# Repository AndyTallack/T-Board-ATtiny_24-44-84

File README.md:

T-Board-Atiny 24/44/84
======================

T-Board for use on Breadboard - Attiny 24/44/84

This is a series of boards to speed up development of your own standalone ATMega/ATTiny projects.  The T-Board houses the microprocessor, power-supply and FTDI interface, with a breadboard-compatible footprint.  This allows you to get up and running fast with the core ATMega/ATTiny "heart" of your project.

This board is based on the great Arduino concept, and is compatible with the Arduino IDE.  It differs in that it:
- allows you to switch between 3.3V and 5V
- allows you to select crystals for low-power applications
- fits snugly into a breadboard, keeping your project together

There are 2 sets of schematic:
- T-Board-44-84 Etch:	1-layer, for hand-etching.  No ICSP header
- T-Board-44-84 PCB:	2-layer, for production-house.  With ICSP header

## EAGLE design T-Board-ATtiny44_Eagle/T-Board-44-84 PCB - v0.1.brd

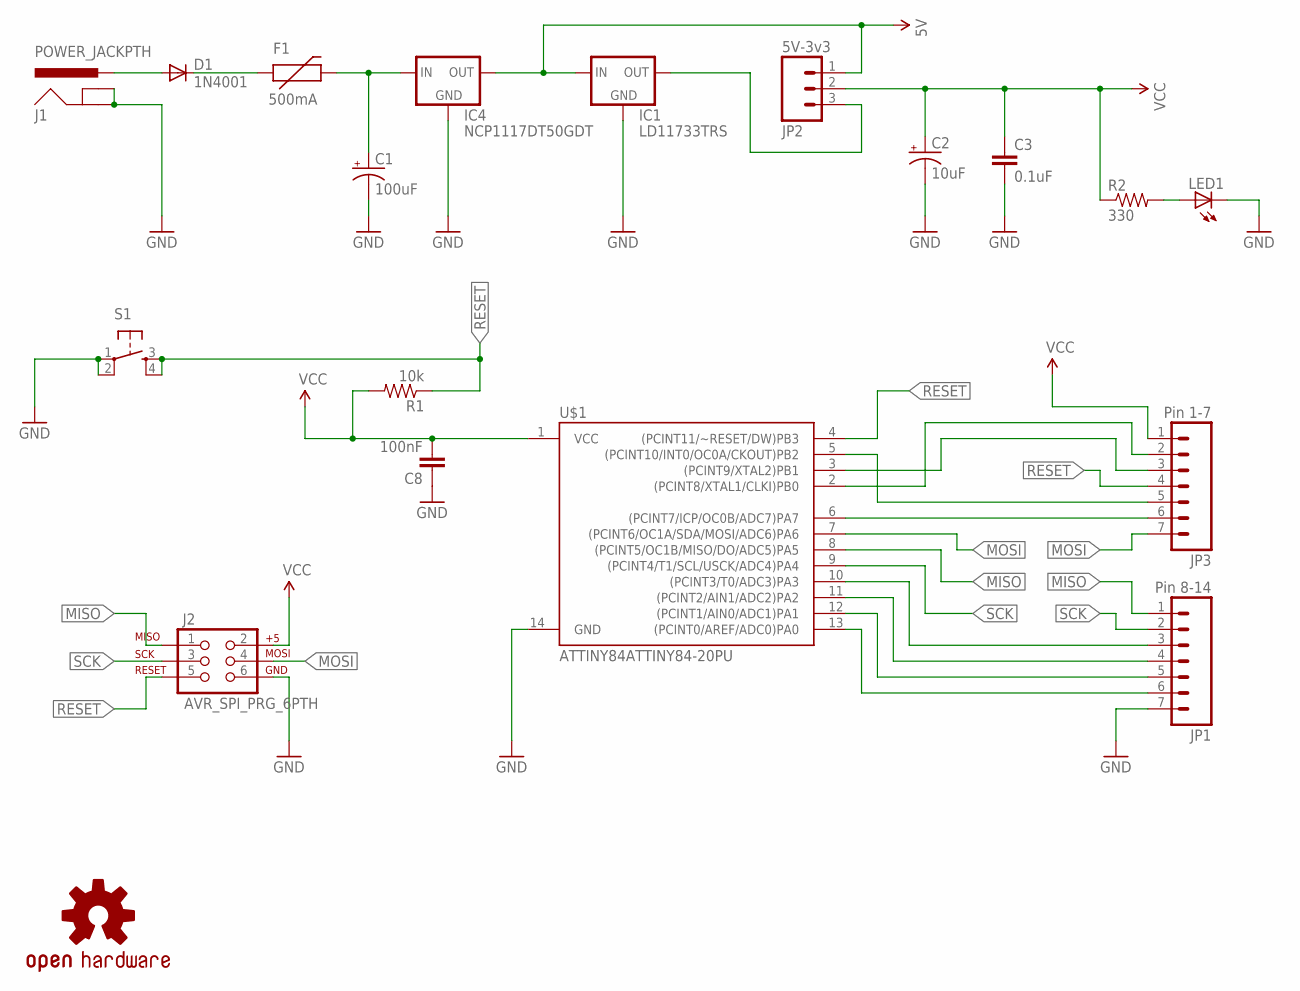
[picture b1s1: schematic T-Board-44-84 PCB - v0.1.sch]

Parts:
C1: 100uF; CPOL-RADIAL-100UF-25V
C2: 10uF; CPOL-RADIAL-10UF-25V
C3: 0.1uF; 1206
C8: 100nF; 1206
D1: 1N4001; DIODE-1N4001
F1: 500mA; PTC
IC1: LD11733TRS; SOT223
IC4: NCP1117DT50GDT; DPACK
J1: POWER_JACKPTH; POWER_JACK_PTH
J2: AVR_SPI_PRG_6PTH; 2X3
JP1: Pin 8-14; 1X07
JP2: 5V-3v3; 1X03
JP3: Pin 1-7; 1X07
LED1: LED1206; LED-1206
LOGO1: OSHW-LOGOS; OSHW-LOGO-S
R1: 10k; 1206
R2: 330; 1206
S1: TAC_SWITCHPTH; TACTILE-PTH
U$1: ATTINY84ATTINY84-20PU; DIL14

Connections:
5V: IC1.3 (IN), IC4.4 (OUT), JP2.1
GND: C1.2 (-), C2.2 (-), C3.2, C8.1, IC1.1 (GND), IC4.1 (GND), J1.GND, J1.GNDBREAK, J2.6, JP1.7, LED1.C, S1.1, S1.2, U$1.14 (GND)
MISO: J2.1, JP1.1, U$1.8 ((PCINT5/OC1B/MISO/DO/ADC5)PA5)
MOSI: J2.4, JP3.7, U$1.7 ((PCINT6/OC1A/SDA/MOSI/ADC6)PA6)
unnamed: D1.A, J1.PWR
unnamed: D1.C, F1.P$1 (1)
unnamed: C1.1 (+), F1.P$2 (2), IC4.3 (IN)
unnamed: JP3.2, U$1.2 ((PCINT8/XTAL1/CLKI)PB0)
unnamed: JP3.3, U$1.3 ((PCINT9/XTAL2)PB1)
unnamed: JP3.5, U$1.5 ((PCINT10/INT0/OC0A/CKOUT)PB2)
unnamed: JP3.6, U$1.6 ((PCINT7/ICP/OC0B/ADC7)PA7)
unnamed: LED1.A, R2.2
unnamed: IC1.4 (OUT), JP2.3
unnamed: JP1.3, U$1.10 ((PCINT3/T0/ADC3)PA3)
unnamed: JP1.4, U$1.11 ((PCINT2/AIN1/ADC2)PA2)
unnamed: JP1.5, U$1.12 ((PCINT1/AIN0/ADC1)PA1)
unnamed: JP1.6, U$1.13 ((PCINT0/AREF/ADC0)PA0)
RESET: J2.5, JP3.4, R1.1, S1.3, S1.4, U$1.4 ((PCINT11/~RESET/DW)PB3)
SCK: J2.3, JP1.2, U$1.9 ((PCINT4/T1/SCL/USCK/ADC4)PA4)
VCC: C2.1 (+), C3.1, C8.2, J2.2, JP2.2, JP3.1, R1.2, R2.1, U$1.1 (VCC)

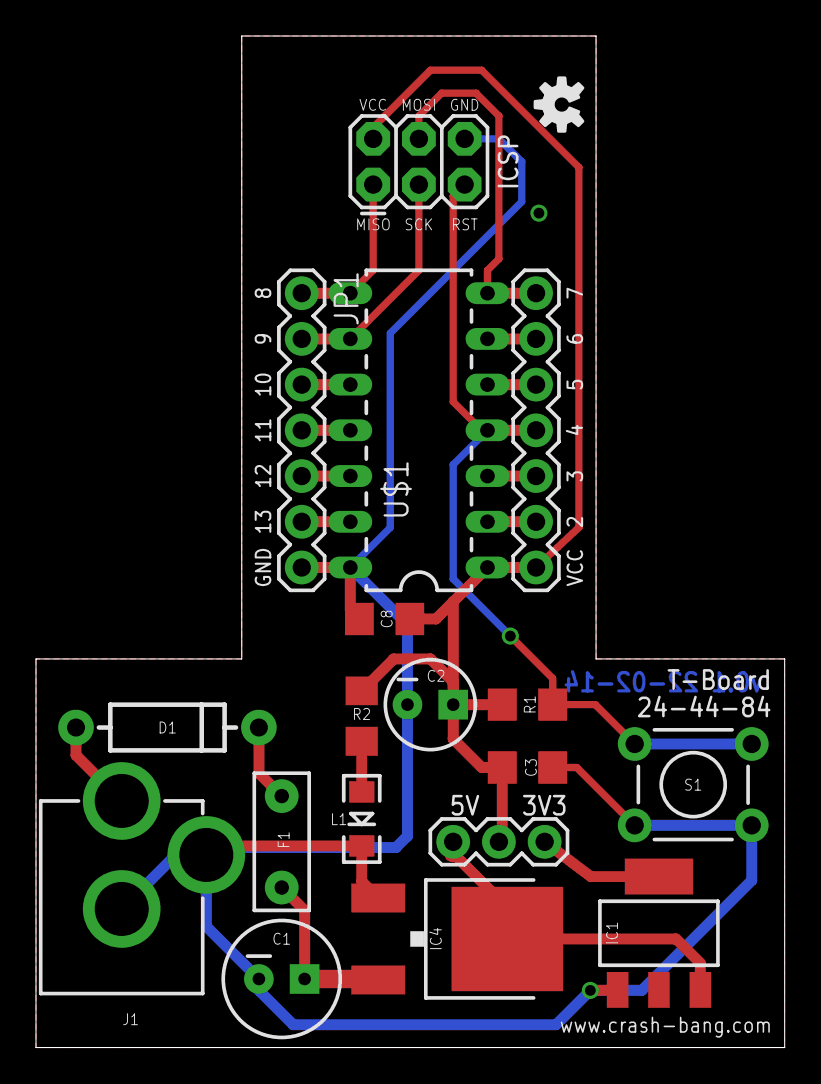
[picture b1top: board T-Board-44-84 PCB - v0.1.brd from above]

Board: 2 copper layers, 41.6 x 56.2 mm, 19 parts (0 on the bottom side), 20 nets.

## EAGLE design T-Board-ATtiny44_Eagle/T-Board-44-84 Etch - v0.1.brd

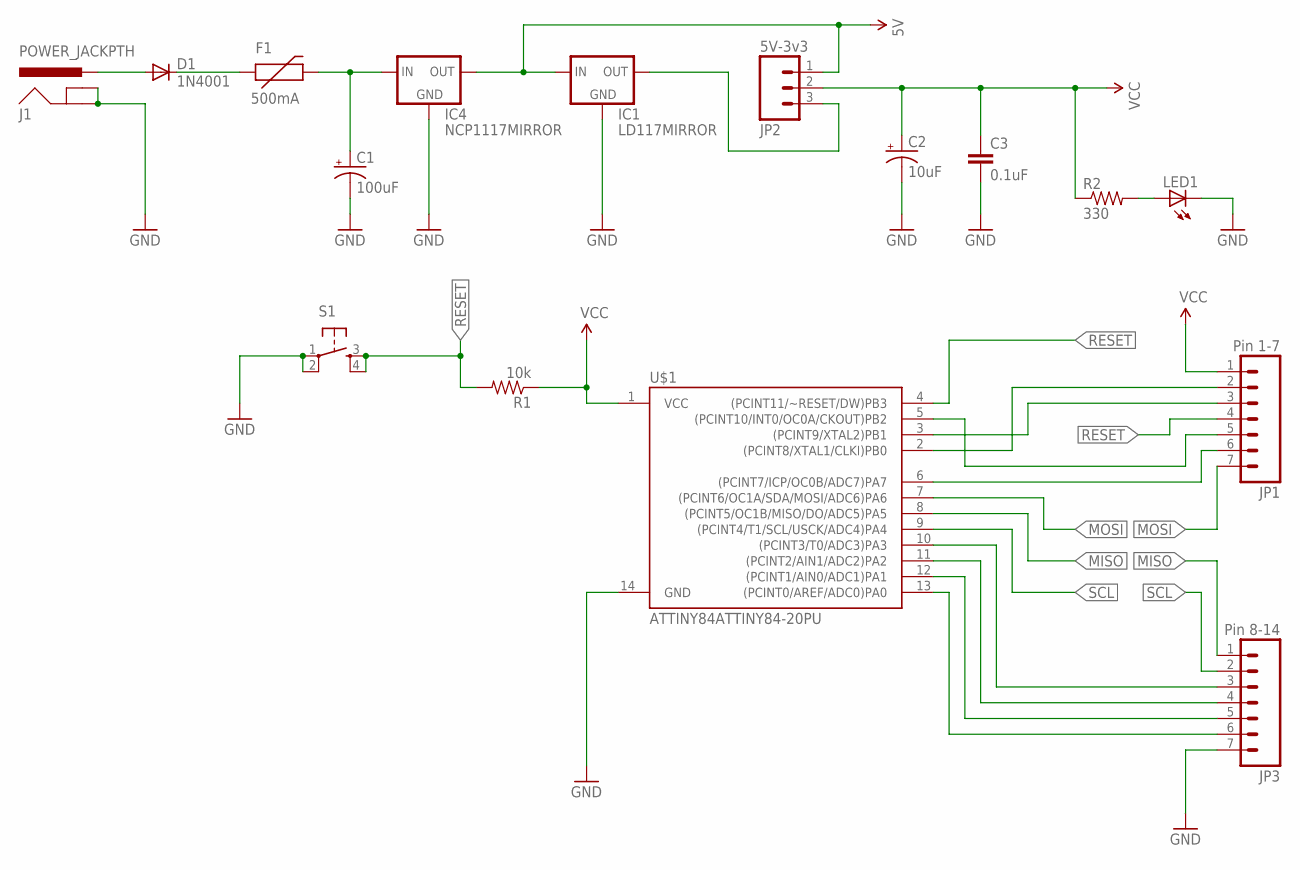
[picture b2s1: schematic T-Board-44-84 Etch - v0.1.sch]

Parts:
C1: 100uF; CPOL-RADIAL-100UF-25V
C2: 10uF; CPOL-RADIAL-10UF-25V
C3: 0.1uF; 1206
D1: 1N4001; DIODE-1N4001
F1: 500mA; PTC
IC1: LD117MIRROR; SOT223
IC4: NCP1117MIRROR; DPACK
J1: POWER_JACKPTH; POWER_JACK_PTH
JP1: Pin 1-7; 1X07
JP2: 5V-3v3; 1X03
JP3: Pin 8-14; 1X07
LED1: LED1206; LED-1206
R1: 10k; 1206
R2: 330; 1206
S1: TAC_SWITCHPTH; TACTILE-PTH
U$1: ATTINY84ATTINY84-20PU; DIL14

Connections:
5V: IC1.1 (IN), IC4.4 (OUT), JP2.1
GND: C1.2 (-), C2.2 (-), C3.2, IC1.3 (GND), IC4.3 (GND), J1.GND, J1.GNDBREAK, JP3.7, LED1.C, S1.1, S1.2, U$1.14 (GND)
MISO: JP3.1, U$1.8 ((PCINT5/OC1B/MISO/DO/ADC5)PA5)
MOSI: JP1.7, U$1.7 ((PCINT6/OC1A/SDA/MOSI/ADC6)PA6)
unnamed: D1.A, J1.PWR
unnamed: JP1.2, U$1.2 ((PCINT8/XTAL1/CLKI)PB0)
unnamed: D1.C, F1.P$1 (1)
unnamed: C1.1 (+), F1.P$2 (2), IC4.1 (IN)
unnamed: JP1.3, U$1.3 ((PCINT9/XTAL2)PB1)
unnamed: JP3.3, U$1.10 ((PCINT3/T0/ADC3)PA3)
unnamed: JP1.6, U$1.6 ((PCINT7/ICP/OC0B/ADC7)PA7)
unnamed: JP3.4, U$1.11 ((PCINT2/AIN1/ADC2)PA2)
unnamed: LED1.A, R2.2
unnamed: IC1.4 (OUT), JP2.3
unnamed: JP3.5, U$1.12 ((PCINT1/AIN0/ADC1)PA1)
unnamed: JP3.6, U$1.13 ((PCINT0/AREF/ADC0)PA0)
unnamed: JP1.5, U$1.5 ((PCINT10/INT0/OC0A/CKOUT)PB2)
RESET: JP1.4, R1.2, S1.3, S1.4, U$1.4 ((PCINT11/~RESET/DW)PB3)
SCL: JP3.2, U$1.9 ((PCINT4/T1/SCL/USCK/ADC4)PA4)
VCC: C2.1 (+), C3.1, JP1.1, JP2.2, R1.1, R2.1, U$1.1 (VCC)

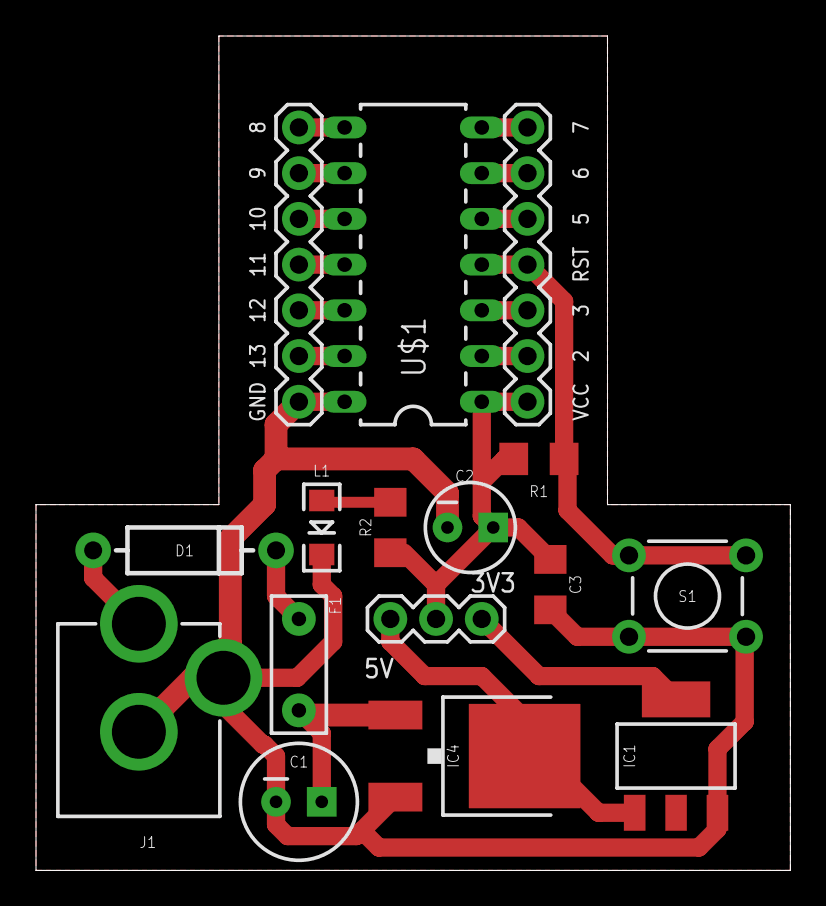
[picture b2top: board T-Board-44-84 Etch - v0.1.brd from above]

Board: 2 copper layers, 41.9 x 46.4 mm, 16 parts (0 on the bottom side), 20 nets.

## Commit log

2014-02-14 v0.1 Prototype
    Prototype untested
2014-03-16 v0.2 - 2 sided proto
    2-sided prototype send to OSHPark to fab. Includes:
    - ICSP header
    - Consistency in trace width
2014-04-11 Adjusted header pins
    Header pins spacing corrected to fit breadboard more precisely

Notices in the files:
parts and their libraries:
SparkFun-Connectors: Licensing: CC v3.0 Share-Alike You are welcome to use this library for commercial purposes.
